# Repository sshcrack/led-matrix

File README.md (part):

<div align="center">

# LED Matrix Controller

**Turn a Raspberry Pi and a few HUB75 LED panels into a calm, good-looking ambient display.**
Aquariums, planets, auroras, music-reactive scenes and self-playing games. Controlled from your phone, with no coding required.

[Quick start](#quick-start) ·
[What is this?](#what-is-this) ·
[Hardware](#hardware) ·
[Install guide](#install-guide) ·
[Desktop app](#desktop-app) ·
[Web UI](#web-ui) ·
[Configuration](#configuration) ·
[Troubleshooting](#troubleshooting) ·
[Development](#development)

</div>

---

## Quick start

> [!IMPORTANT]
> **You need:** a **Raspberry Pi 3 or 4** (the Pi 5 is untested, see [Shopping list](#shopping-list)), a microSD card of **8 GB or more**, HUB75 LED panels, a HUB75 adapter board or HAT, and a separate **5 V supply** for the panels.

| I have… | Do this |
|:--|:--|
| A Pi with panels wired up | Follow the steps below (about 15 minutes, most of it waiting) |
| A Pi already running Raspberry Pi OS that I want to keep | [**Install the package**](#install-on-an-existing-raspberry-pi-os) |
| A Pi with panels, and I'd rather have an AI agent do it | [**Set up with an AI agent**](#set-up-with-an-ai-agent) |
| Nothing yet (no Pi, panels or adapter) | [**Hardware**](#hardware): what to buy and how to wire it |
| Just a computer, no hardware | [**Try the emulator**](#try-it-without-hardware) |

### 1. Flash the card

The panel image is Raspberry Pi OS Lite (64-bit) with everything installed. Its system is read-only, so the panel can be unplugged like any appliance ([details](docs/PI_IMAGE.md)).

1. Download Raspberry Pi Imager and start it with this project's image list, in one command:

   | OS | Run |
   |:--|:--|
   | **Linux / macOS** | `curl -fsSL https://raw.githubusercontent.com/sshcrack/led-matrix/master/scripts/flash_card.sh \| bash` |
   | **Windows** (PowerShell) | `irm https://raw.githubusercontent.com/sshcrack/led-matrix/master/scripts/flash_card.ps1 \| iex` |

   The script ([`flash_card.sh`](scripts/flash_card.sh), [`flash_card.ps1`](scripts/flash_card.ps1)) fetches the current Imager (version 2 or newer; on Linux and macOS it is cached and not installed system-wide) and runs `rpi-imager --repo https://github.com/sshcrack/led-matrix/releases/latest/download/led-matrix-imager.json`. If you already have Imager, run that command yourself, or enter the URL under **App Options → Content Repository → Use custom URL**.
2. Choose your Pi model, then **LED Matrix** as the operating system, and your SD card.
3. In the customisation, set a username and password, your **Wi-Fi** (skip it for Ethernet) and, if you want to log in later, **SSH**. Set the hostname to **`led-matrix`** (Imager may suggest another name), or remember the one you choose.
4. Write the card, put it in the Pi and power it on. The first boot takes a few minutes and restarts once.

The image and its checksum are also on the [Releases](https://github.com/sshcrack/led-matrix/releases/latest) page (`led-matrix-<version>-arm64.img.xz`) if you prefer another flashing tool. Imager is still needed for the Wi-Fi and user settings.

### 2. Set up the panel

Open **`http://led-matrix.local:8080/`** on a phone or computer on the same network (or `http://<pi-ip-address>:8080/`; your router shows the address). On a phone, use *Add to Home Screen* to install it like an app.

The page asks you to **set up your panel**. The image starts with settings for four 64×64 panels in a 2×2 grid (two chains of two, 128×128 pixels) on a Pi 3. On the **Panel hardware** card:
1. Switch on **Show test pattern**. If the picture is already right, press **Looks right** and you are done.
2. Otherwise choose your layout under **Change panel settings**. Use GPIO slowdown `3` for a Pi 3 and `2` for a Pi 4.
3. Apply. The panel restarts with the new settings, and goes back to the old ones by itself if it does not come up.

The settings are right when the red corner is top left, the arrow points up and the white frame runs round the whole picture. Other layouts are in [Working out the numbers](#working-out-the-numbers).

### 3. Use it

1. Press the power button (top right) if the matrix is off.
2. In **Control**, leave the toggle on **Auto** to let the Director pick scenes, or pick **Manual** and click a preset.
3. Press **+** to build a preset: choose a one-tap starting point (Night sky, Digital calm, Desk clock) or pick scenes yourself.
4. Open **Scenes** to browse every scene with an animated preview.

Panels dark, flickering or scrambled? Those are almost always one-flag fixes. See [Troubleshooting](#troubleshooting).

### 4. Optional: the desktop app on your PC

The [desktop app](#desktop-app) adds music reactivity (from your PC's audio output), GPU shader scenes, music videos, and render offload for heavy scenes. It installs for your user only, with no admin rights, and keeps itself on the same version as your matrix.

| OS | Install |
|:--|:--|
| **Windows** | Run `led-matrix-desktop-<version>-win64.exe` from [Releases](https://github.com/sshcrack/led-matrix/releases/latest) |
| **Linux** (x86_64) | `curl -fsSL https://raw.githubusercontent.com/sshcrack/led-matrix/master/scripts/install-desktop.sh \| sh` |

Start it and click **Connect**. It looks for the panel at `led-matrix.local` (port `8080`); enter the Pi's address instead if you changed the hostname or installed the package yourself.

### Install on an existing Raspberry Pi OS

Use this instead of the image when the Pi already runs **64-bit** Raspberry Pi OS (Lite) with a user named **`pi`**.

#### Prepare the Pi (one-time)

SSH into the Pi. Its onboard sound shares hardware with the LED driver, so turn it off, as the upstream library recommends:

```bash
echo "blacklist snd_bcm2835" | sudo tee /etc/modprobe.d/blacklist-rgb-matrix.conf
sudo sed -i 's/^dtparam=audio=on/dtparam=audio=off/' /boot/firmware/config.txt   # /boot/config.txt on older images
sudo reboot
```

#### Install the package

```bash
# Download the installer, read it if you like, then run it
curl -fsSLO https://raw.githubusercontent.com/sshcrack/led-matrix/master/scripts/install_led_matrix.sh
bash install_led_matrix.sh
```

The installer downloads the latest `.deb` from [Releases](https://github.com/sshcrack/led-matrix/releases/latest), installs it and starts the service. It asks for:

| Question | What to answer |
|:--|:--|
| Rows / columns per panel | Panel size, e.g. `64` and `64` |
| Chained panels | Panels daisy-chained on one cable (this sets the width) |
| Parallel chains | Number of cables from the adapter (this sets the height) |
| GPIO slowdown | `3` for a Pi 3, `2` for a Pi 4 |
| Spotify, API token, auto-updates | Optional. You can skip all of them and set them up later |

Four 64×64 panels in a 2×2 grid are `64` / `64` / `2` / `2`. Other layouts are in [Working out the numbers](#working-out-the-numbers).

Then open **`http://<pi-ip-address>:8080/`** (the installer prints the address) and continue with [Use it](#3-use-it).

### Set up with an AI agent

Coding agents (Claude Code, Codex, Cursor, …) can do the whole setup for you, including the interview about your panels. Run the agent on the computer where you want the [desktop app](#desktop-app) (Windows or Linux). If the card isn't flashed yet, it walks you through flashing the panel image with SSH enabled; otherwise make sure you can `ssh` into the Pi from that computer. The agent sets up the Pi over SSH, then installs the desktop app on that computer and connects it to the Pi. Paste:

```text
Set up my LED matrix. Read and follow
https://raw.githubusercontent.com/sshcrack/led-matrix/master/docs/AGENT_SETUP.md
Interview me first, then install and verify everything yourself.
```

The [agent setup guide](docs/AGENT_SETUP.md) is written for machines. It has an interview script that maps your answers to the right flags, a non-interactive install, verification checks, a flicker and colour troubleshooting tree, and rules for handling secrets safely.

### Try it without hardware

The emulator runs the same code as the Pi and shows the matrix in a browser tab, so you can try everything before buying anything. It is built from source (Linux x86_64, see the [build prerequisites](#build-prerequisites)):

```bash
git clone --recurse-submodules https://github.com/sshcrack/led-matrix.git
cd led-matrix
cmake --preset emulator
cmake --build --preset emulator --target install
./scripts/run_web_emulator.sh              # then open http://localhost:8080/web/
```

---

## What is this?

A passive piece of light art for your wall or desk. It runs a growing collection of scenes, picks what to show on its own, and reacts to the music you play. The display shows no tickers and takes no input from viewers. You set it up once and then mostly forget about it.

- **Automatic Mode.** A Director chooses from curated scene looks and composes 24–36 minute visual arcs. While music plays it favours music-reactive scenes. Switch to **Manual** to play your own presets.
- **Follows the real world.** Outdoor scenes match the time of day, weather, season and holidays where the matrix is.
- **Web UI** that works on phones and desktops, installable as a PWA. It has a live 128×128 preview, a scene gallery, a Scene Lab, schedules and diagnostics. See the [tour](#web-ui).
- **Desktop app** (Windows and Linux) for the heavy lifting: GPU shaders, system-audio capture, YouTube music videos. Your PC does the rendering and the Pi just displays pixels. See [Desktop app](#desktop-app).
- **Runs on modest hardware.** Scene quality adapts to the Pi's measured load, and heavy scenes can move to your PC automatically.
- **One `.deb` to install.** A systemd service, safe self-updates with automatic rollback, and a REST API for everything.

```mermaid
flowchart LR
    subgraph Browser["Phone / browser"]
        WEB["Web UI (PWA)"]
    end
    subgraph Pi["Raspberry Pi"]
        D["led-matrix daemon<br/>scenes · Director · REST API"]
        P[("HUB75 LED panels")]
        D -- GPIO --> P
    end
    subgraph PC["Your PC (optional)"]
        APP["Desktop app<br/>audio capture · shaders · video"]
        W["Scene worker<br/>full-quality offload"]
    end
    WEB -- "HTTP + WebSocket :8080" --> D
    APP -- "WebSocket (config, audio analysis)" --> D
    APP -- "UDP pixel stream" --> D
    W -- "rendered frames" --> D
```

---

## Showcase

<div align="center">

<sub>The web UI: Control → Scenes → Lab → Automation → Health, plus the ⌘K palette.</sub>

</div>

<details>
<summary><b>More scene previews</b> (about 10 MB of animated GIFs)</summary>

<br>

Previews are hosted on the rolling [`scene-previews` release](https://github.com/sshcrack/led-matrix/releases/tag/scene-previews) to keep the git history small. The web UI shows all of them.

<div align="center">

<table>
<tr><td align="center"><br><sub><b>Aurora</b> · shader</sub></td><td align="center"><br><sub><b>Tidal Aquarium</b> · shader</sub></td><td align="center"><br><sub><b>Planetary Vista</b> · shader</sub></td><td align="center"><br><sub><b>Volcano</b> · music-reactive</sub></td></tr>
<tr><td align="center"><br><sub><b>Night Drive</b> · music-reactive</sub></td><td align="center"><br><sub><b>Campfire</b> · music-reactive</sub></td><td align="center"><br><sub><b>Lighthouse</b> · music-reactive</sub></td><td align="center"><br><sub><b>Celestial Bloom</b> · music shader</sub></td></tr>
<tr><td align="center"><br><sub><b>Neon Tunnel</b></sub></td><td align="center"><br><sub><b>Reaction Diffusion</b></sub></td><td align="center"><br><sub><b>Metablob</b></sub></td><td align="center"><br><sub><b>Koi Pond</b> · follows the seasons</sub></td></tr>
</table>

</div>

</details>

---

## Hardware

> [!NOTE]
> This project builds on the excellent [rpi-rgb-led-matrix](https://github.com/hzeller/rpi-rgb-led-matrix) library by Henner Zeller. For wiring diagrams, timing issues and panel quirks, its documentation is the reference.

### Shopping list

| Part | Recommendation |
|:--|:--|
| **Computer** | **Raspberry Pi 4** (best), or Pi 3 B/B+ (works, and the maintainer's 128×128 runs on a Pi 3 B with adaptive quality and desktop offload). A 64-bit OS is required. The Pi 5 is supported by the LED library since [v0.1.13](https://github.com/sshcrack/rpi-rgb-led-matrix/releases/tag/v0.1.13) (RP1 backend, `--led-rp1-pio`), but this app has not been tested on one. |
| **Panels** | HUB75 RGB panels. **Four 64×64 panels in a 2×2 grid make a 128×128 display**, which is the primary target. 32×32 and 64×32 panels work too, and scenes read the canvas size. |
| **Adapter** | A HAT or bonnet that level-shifts GPIO to HUB75, e.g. the [Electrodragon Active-3](https://www.electrodragon.com/product/rgb-matrix-panel-drive-board-raspberry-pi/). [Alternatives](https://github.com/hzeller/rpi-rgb-led-matrix/blob/master/adapter/README.md). |
| **Power** | A dedicated **5 V** supply for the panels, sized generously. Panels can draw several amps each at full white. Power the Pi separately and share ground. Don't power panels from the Pi. |
| **Cables** | The HUB75 ribbon cables that come with the panels, plus power leads for each panel. |
| **Storage** | A microSD card, 16 GB or more. |

### Working out the numbers

The matrix size is **width = `cols` × `chain`** and **height = `rows` × `parallel`**.

| Layout | rows | cols | chain | parallel | Result |
|:--|:-:|:-:|:-:|:-:|:--|
| Four 64×64 panels, 2×2 *(recommended)* | 64 | 64 | 2 | 2 | 128×128 |
| One 64×64 panel | 64 | 64 | 1 | 1 | 64×64 |
| Two 64×32 panels side by side | 32 | 64 | 2 | 1 | 128×32 |
| Four 32×32 panels in a row | 32 | 32 | 4 | 1 | 128×32 |

The installer asks for these. They end up as `--led-rows`, `--led-cols`, `--led-chain` and `--led-parallel` in `/etc/default/led-matrix`. How many parallel chains your adapter supports depends on the adapter, so check its documentation. The Active-3 has three parallel outputs.

### Assemble and wire

1. Plug the **adapter or HAT** onto the Pi's 40-pin header (Pi switched off and unplugged).
2. Connect the adapter's HUB75 output to the **input** of the first panel with the ribbon cable. Panels have an *in* and an *out* side, usually marked with an arrow.
3. For more panels on the same chain, run a ribbon from the first panel's **output** to the next panel's **input**. Use a second adapter output for a second (parallel) chain. Which output is which depends on the adapter, so check its documentation, or the upstream [wiring guide](https://github.com/hzeller/rpi-rgb-led-matrix/blob/master/wiring.md).
4. Connect the **5 V supply** to every panel's power connector (use the supplied power leads). Power the Pi from its own supply. Power everything off before changing any cable.

### Flash the Pi

Flash the panel image as described in [Flash the card](#1-flash-the-card). To use plain Raspberry Pi OS instead, choose **Raspberry Pi OS Lite (64-bit)** in Imager, set the username **`pi`**, Wi-Fi and SSH in its customisation, and continue with [Install on an existing Raspberry Pi OS](#install-on-an-existing-raspberry-pi-os).

> [!TIP]
> Prefer not to do this alone? Your [AI agent](#set-up-with-an-ai-agent) can walk you through every step above and run the commands over SSH.

---

## Install guide

The [Quick start](#quick-start) covers a normal install. This section is the reference for what gets installed and how to change, update or remove it.

### Requirements

- Raspberry Pi 3 or 4 (Pi 5 untested) with a **64-bit** Debian-based OS (Debian 12 "Bookworm" or newer), a user named **`pi`**, and internet access
- Panels wired and powered (see [Hardware](#hardware))
- The Pi's onboard sound disabled ([Prepare the Pi](#prepare-the-pi-one-time))

### Install

Use the [installer script](#install-the-package), or install the package yourself:

```bash
# Download led-matrix-<version>_arm64.deb from the latest release, then:
sudo apt install ./led-matrix-*_arm64.deb
```

Either way, the package:

- installs the daemon to `/usr/bin/led-matrix`, with plugins, web UI and previews under `/usr/lib/led-matrix` and `/usr/share/led-matrix`
- writes your answers to `/etc/default/led-matrix`
- creates `/var/lib/led-matrix/` (config, uploads, crash reports), owned by `pi`
- enables and starts `led-matrix.service` and the updater units

The service starts as root (needed for GPIO) and drops privileges to `pi:pi` as soon as the matrix is initialised.

### Check that it works

```bash
systemctl status led-matrix          # should be active (running)
curl -s localhost:8080/status        # {"turned_on":true, ...}
journalctl -u led-matrix -f          # live logs
```

### Change settings later

> [!IMPORTANT]
> `/etc/default/led-matrix` is **regenerated from the stored answers on every upgrade and reconfigure**, so manual edits to it are lost. Change settings through debconf.

```bash
sudo dpkg-reconfigure led-matrix     # re-asks every question
```

Or non-interactively:

```bash
echo "led-matrix led-matrix/led-slowdown-gpio string 2" | sudo debconf-set-selections
echo "led-matrix led-matrix/extra-opts string --led-brightness=60" | sudo debconf-set-selections
sudo DEBIAN_FRONTEND=noninteractive dpkg-reconfigure led-matrix
```

Any extra [rpi-rgb-led-matrix flag](https://github.com/hzeller/rpi-rgb-led-matrix?tab=readme-ov-file#types-of-displays) goes in `extra-opts`.

### Update and uninstall

Updates run automatically if you enabled them. You can also use the **Updates** page or `POST /api/update/install`. Each update is unpacked as its own version in `/var/lib/led-matrix-app` and switched to in one step; a version that does not come up healthy is switched back automatically ([details](docs/transactional-updates.md)). Manually: install a newer `.deb` with `sudo apt install ./led-matrix-*.deb`.

```bash
sudo apt remove led-matrix           # keep your data
sudo apt purge led-matrix            # also removes /var/lib/led-matrix and the stored answers
```

### Power-cut-safe card (optional)

The [panel image](#1-flash-the-card) is already power-cut-safe. To move an existing install to such a card, `packaging/pi-image/` exports the settings from the running Pi and builds an image with them. See [docs/PI_IMAGE.md](docs/PI_IMAGE.md). Updates of the app work as usual there (they go to the data partition); OS updates go through `sudo led-matrix-system-mode writable`.

---

## Desktop app

The Pi is deliberately modest. The **desktop app** gives it superpowers by running on a PC on the same network:

| It adds… | How it works |
|:--|:--|
| **Music reactivity** | Captures your system's audio output (WASAPI loopback on Windows, PipeWire/PulseAudio monitor on Linux), analyses it (spectrum, beats, drops, BPM, sections) and streams the result to the Pi. No microphone needed. |
| **GPU shaders** | Renders the `shader:*` scenes (Aurora, Aquarium, Planetary Vista…) and streams pixels to the Pi over UDP. Custom `.frag` files can be uploaded in the web UI under **Assets**. |
| **Video and music videos** | `video` plays YouTube and URL videos, and `spotifymv` auto-plays the music video for your current Spotify track. Needs [`yt-dlp`](https://github.com/yt-dlp/yt-dlp) and ffmpeg on the PC. |
| **Render offload** | A background scene worker runs the same scene code at full quality when the Pi is under pressure. The handoff is seamless, with local fallback if the worker disappears. |

<table>
<tr>
<td width="50%"><br><sub>Connected, with audio analysis streaming.</sub></td>
<td width="50%"><br><sub>The scene worker is running and ready to take over heavy scenes.</sub></td>
</tr>
</table>

### Install

Grab the latest build from [Releases](https://github.com/sshcrack/led-matrix/releases/latest):

| OS | Install (for your user, no admin/root) |
|:--|:--|
| **Windows** | Run `led-matrix-desktop-<version>-win64.exe`, or `irm https://raw.githubusercontent.com/sshcrack/led-matrix/master/scripts/install-desktop.ps1 \| iex` |
| **Linux** (x86_64) | `curl -fsSL https://raw.githubusercontent.com/sshcrack/led-matrix/master/scripts/install-desktop.sh \| sh` (add `-s -- <version>` after `sh` for a specific version). Or download `led-matrix-desktop-<version>-Linux.tar.gz`, extract it and run `bin/led-matrix-desktop --install` |

On Linux the installer adds a launcher entry and `~/.local/bin/led-matrix-desktop`; put `~/.local/bin` on your `PATH` to start it from a terminal.

The app installs to `%LOCALAPPDATA%\led-matrix-desktop` or `~/.local/share/led-matrix-desktop` and **updates itself**: it runs the same release as your matrix (offload requires compatible protocol and scene contracts). When a newer release is out and the matrix has auto-update on, it asks the matrix to update first and follows it. Updates download in the background and apply when the app is hidden in the tray or restarted. You can turn this off in the app menu. An older `.deb` or admin install is replaced on its first update, and the app offers to remove it. Uninstall with `led-matrix-desktop --uninstall` or from Windows *Installed apps*.

### Use

1. Start the app, enter the Pi's **hostname or IP** and the **port** (`8080`), and add the **API token** if you set one.
2. Click **Connect**. The status switches to *WebSocket is currently: Open* and the plugin tabs show what is active.
3. Leave it running in the tray. Enable *Turn Matrix On on Start* if you like.

The app needs to be connected for shader scenes, desktop audio, videos and render offload. Everything else keeps working without it.

---

## Web UI

Open `http://<pi-ip>:8080/` in any browser. On a phone, use *Add to Home Screen* to install it like an app.

<table>
<tr>
<td width="50%"><br><b>Control.</b> Presets, the live preview, and a one-click Auto/Manual switch. The inspector edits the selected preset in place and autosaves.</td>
<td width="50%"><br><b>Scenes.</b> Browse every scene with animated previews. Tune what the Director may play: favourite a look, keep it, or switch it off.</td>
</tr>
<tr>
<td><br><b>Lab.</b> Try scenes on the real Pi renderer with temporary controls. Nothing is saved until you decide.</td>
<td><br><b>Automation.</b> Time-of-day schedules and a night-brightness fade.</td>
</tr>
<tr>
<td><br><b>Health.</b> Renderer FPS, transport stats, and a transparent view of why the Director chose what it chose.</td>
<td><br><b>Quick builder.</b> Create <i>and play</i> a preset in one step from one-tap starting points or any scenes you pick.</td>
</tr>
</table>

Press <kbd>Ctrl</kbd>/<kbd>⌘</kbd>+<kbd>K</kbd> anywhere for the command palette, and use the sun/moon button for the light theme.

<details>
<summary><b>On your phone, and in light mode</b></summary>

<br>

<div align="center">

<br><br>

</div>

On screens narrower than 1024 px the layout switches to a bottom tab bar with an always-visible mini-player, and editors open as bottom sheets.

</details>

---

## Features

### Scenes

Scenes are supplied by plugins. Native scenes render on the Pi or desktop worker; shader and video scenes need the desktop app. Browse **Scenes** in the web UI for the installed catalog.

| Category | Highlights |
|:--|:--|
| **Audio reactive** | A spectrum analyser and small scenic worlds that dance to the music: campfire, volcano, lighthouse, reef, skate park, tesla coil, night drive, roller rink… plus `music_director`, an automatic DJ |
| **Shaders** | GPU scenes rendered on your PC: Aurora, Tidal Aquarium, Planetary Vista, Plasma Garden, and music shaders (Celestial Bloom, Subwoofer, Tube Amp…). Add your own `.frag` files |
| **Hobbies & activities** | Hiking trails and an alpine lake, horses in the mist, basketball and football, and cycling a coast road or skiing a slope |
| **Ambient** | A forest path and a cottage that change with the seasons, a Christmas market and a sleigh over a snowy village (December only in Automatic Mode), a starling murmuration over a wetland at dusk, plus Starfield, Metablob, Clock, Neon Tunnel, Rain |
| **Games** | Self-playing Tetris |
| **Generative** | Reaction-diffusion, Falling Sand, Watermelon Plasma |
| **Fractals** | Julia set, Game of Life |
| **Particles** | Rain, Sparks |
| **Media** | YouTube music videos that follow your Spotify track, a video player, and Spotify cover art when connected |
| **Weather** | Live weather (via Open-Meteo, no API key) |
| **Utility / Images** | Countdown with fireworks, and a pixel-art and image provider |

Plus **7 post-processing effects** (flash, rotate, glow, RGB split, glitch, pixelate, shockwave; they can fire on beats) and **11 transitions** (blend, swipe, morph, radial reveal, dissolves, CRT collapse, …).

### Control

| Feature | What it does |
|:--|:--|
| **Automatic Mode** | The Director picks from curated looks, plans long arcs, and uses music state when it is available. Every look can be starred or excluded in the Scenes page. Pick a style on the home screen: **Mixed** (everything, music first), **Outside** (calm scenery that matches the real time, weather, season and holidays), **Party** (energetic music looks, quicker cuts) or **Chill** (slow and soft, long dwell). Holiday scenes such as the Christmas market only play while their holiday is on. |
| **Presets** | Ordered lists of scenes with per-scene properties and transitions. Edits autosave, and deleting a preset can be undone. Three one-tap ambiance packs are included. |
| **Scene Lab** | Try a scene or curated look on the real Pi renderer with temporary controls, then save it only if you like it. |
| **Schedules** | Switch presets by time and weekday (overnight ranges work) and dim the panel at night with a smooth brightness fade. While *Auto Scheduling* is on, an active schedule takes over from Automatic Mode, and the display turns **off** outside every schedule window. Add windows for all the hours you want lit, or leave it off. |
| **Real-world scenery** | Outdoor scenes follow the real time of day, weather and season where the matrix is: sunset light, rain, fog, snow on the ground, autumn leaves, decorations at Christmas. The location is detected from the IP address or set by city. You can override it for every scene (snow all winter, always night) or pin a single scene, or turn it off. See [Real-world scenery](#real-world-scenery-optional). |
| **Live preview** | A real-time view of the composed matrix frame, pulled on demand so an idle page costs the Pi nothing. |
| **Plugin UIs** | Plugins can ship their own web controls, for example the YouTube playlist editor. |
| **Safe updates** | Check and install updates from the UI. The updater health-checks the new version and rolls back automatically on failure ([details](docs/transactional-updates.md)). The desktop app updates itself to the same release. |
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
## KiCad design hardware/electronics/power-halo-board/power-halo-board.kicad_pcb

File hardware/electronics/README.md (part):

# Electronics: power distribution and halo controller

Status: **prototype design, unvalidated, not approved for fabrication.** Nothing here has been
built or measured. The outputs in `exports/` are marked PROTOTYPE / UNVALIDATED.
[docs/verification.md](docs/verification.md) lists what was checked and what is still open.

## Architecture

The display uses a 2×2 grid of Waveshare P3 64×64 HUB75E panels (1/32 scan, 5 V / 4 A, at most
20 W each). It is driven by a Raspberry Pi 3B through the existing software:
`--led-rows=64 --led-cols=64 --led-chain=2 --led-parallel=2`, the default (`regular`) GPIO
mapping, and address lines A–E.

The design uses **one custom board** plus off-the-shelf parts:

| Part | What it is | Custom? |
|---|---|---|
| 24 V supply | Mean Well GST160A24-R7B: external Class I brick, 160 W, 4-pin power DIN plug | no |
| Enclosure jack | Kycon KPJX-PM-4S panel-mount 4-pin power DIN jack, AWG18 pigtail to J1 | no |
| **Power + halo board** | `power-halo-board/`, 136 × 86 mm, 4 layers | **yes** |
| HUB75 interface | Electrodragon RGB matrix driver board for Raspberry Pi, V2 (the board the main README links) | no |
| Controller | Raspberry Pi 3B (Wi-Fi only) | no |
| Halo | 40 × WS2812B-class LEDs on one 5 V data line | no |

```
230 V ─ brick (outside the enclosure, 24 V SELV) ─ DIN jack ─ AWG18 ─ J1
  J1 ─ F1 8 A ─ LM74700 + PSMN5R2 ideal diode ─ SMBJ30A + bulk ─ +24V
  +24V ─ 4× TPSM63610 → 5.0 V ─ TPS259470A eFuse (5.0 A) ─ J101..J401 ─ panel 1..4 power
  +24V ─ TPSM63610 AUX → +5V_AUX ─┬─ TPS259470A (3.0 A) ─ J501 ─ Electrodragon 5 V in ─ Pi
                                  ├─ TPS259470A (2.6 A, MCU-enabled) ─ J601 ─ halo (+5V, DIN, GND)
                                  └─ ATtiny1616, AHCT buffer, LEDs
  Pi GPIO14 (TXD) ─ 1k ─ AHCT1G125 ─ ATtiny1616 UART RX       (halo commands)
  Pi GPIO26 ─ 1k ─ JP601 ─ BSS138 ×2 ─ EN of the four panel bucks (panel request)
```

Why one board: the brick keeps mains out of the enclosure. The Electrodragon V2 already
buffers HUB75 for two parallel chains with the E line, so a custom HUB75 board would add
nothing. What is missing is protected 5 V power for 85 W of panels plus the Pi and halo, and a
halo driver that uses no matrix pins. One board does both. The decisions behind this:

- **24 V distribution** instead of a 5 V brick. One 5 V rail would carry 18 A or more through
  connectors and wiring. At 24 V the input carries 4.9 A worst case. Each panel gets its own
  converter and its own limit.
- **Hardware current limit per output.** Each panel branch has an eFuse limited to 5.0 A ±10 %
  (the panel is rated 4 A). The Pi and halo branches are limited to 3.0 A and 2.6 A. Software
  brightness limits are not counted as protection anywhere.
- **No backfeed.** Every 5 V output eFuse blocks reverse current. The Pi logic lines only sink
  into the board through 1 kΩ resistors and high-impedance inputs. The board never drives a Pi
  pin.
- **Halo without matrix pins.** It uses GPIO14 (UART TXD) and GPIO26. With
  `--led-parallel=2` the library leaves chain-3 pins free (GPIO 2, 3, 14, 16, 21, 26). The
  ATtiny1616 generates the WS2812 timing, so the Pi only sends short UART commands. The halo
  must never be fed by continuously pushed `/live_frame` capture. The API preview stays
  pull-only.
- **Electrodragon V2 is fine with conditions** (see [docs/wiring.md](docs/wiring.md#hub75-and-the-electrodragon-v2)):
  - Set the E-line selector so pin 8 carries E and pin 4 is GND.
  - Leave its third HUB75 output (P2) unconnected.
  - Power it only from J501.

## Files

| Path | Content |
|---|---|
| `power-halo-board/` | KiCad 9 project: hierarchical schematic (root + Input, Panel ×4, Aux, Halo), routed PCB, project-local symbol and footprint library `lib/`, net classes and rules (`.kicad_pro`, `.kicad_dru`) |
| `power-halo-board/lib/3dmodels/` | VRML envelope boxes for the parts the stock KiCad libraries reference but never shipped a model for (see `tools/gen_3dmodels.py`) |
| `tools/circuit.py` | the circuit as data: every part with value, MPN, manufacturer, datasheet, rating and pin-to-net map |
| `tools/gen_lib.py`, `gen_sch.py`, `gen_project.py` | write the library, schematic and project files from `circuit.py` |
| `tools/gen_pcb.py` | placement, power zones, Freerouting autorouting, ground pours, stitching, silkscreen |
| `tools/check_board.py` | ERC, independent netlist check, DRC with schematic parity, prototype exports |
| `tools/check_netlist.py` | checks every pin-to-net connection of the exported netlist against `circuit.py` |
| `tools/spice/` | ngspice decks (thresholds, enable sequence, hot-plug), runner and `results.txt` |
| `tools/power_budget.py` | worst-case power and thermal budget |
| `tools/gen_envelope.py` | height envelope and plug keepouts as JSON and STEP for the enclosure |
| `tools/gen_3dmodels.py` | `lib/3dmodels/`: envelope box per part whose stock KiCad 3D model does not exist, so the 3D viewer shows every component |
| `docs/wiring.md` | harnesses, pinouts, keying, wire gauge, strain relief, HUB75 and the Electrodragon V2 |
| `docs/power-and-thermal.md` | supply choice, rails and loads, protection, thermal budget, ventilation |
| `docs/mechanical-interface.md` | outline, holes, connector positions and directions, heights, keepouts |
| `docs/verification.md` | what was verified, with results, and the open gaps |
| `docs/bom.csv` | BOM (copied from the export) |

## Board

- 136 × 86 mm, 1.6 mm FR4, 4 layers, ENIG.
- Copper is 2 oz on the outer layers and 1 oz on the inner layers.
- Layers:
  - F.Cu: components, +24 V and 5 V power zones.
  - In1: solid GND.
  - In2: +5V_AUX plane regions, GND elsewhere.
  - B.Cu: signals and a GND pour.
- Net classes:
  - `Power24`: +24V and VIN_*, 0.5 mm, 0.3 mm clearance.
  - `Power5`: panel VOUT/VPANEL, VPI and VHALO, 0.4 mm.
  - `GND`, `Power5AUX`, `Default`: 0.2 mm.
- Custom rules: 24 V clearance 0.3 mm, minimum 0.4 mm power taps, 0.5 mm copper-to-edge.
  Autorouted tracks and vias are additionally kept 0.85 mm from the edge by rule areas.
- The committed `.kicad_pcb` has its **zones unfilled**: filled it is about 1.9 MB, against the
  repo's 2 MiB per-file guard. Press `B` in KiCad, or use `exports/power-halo-board-filled.kicad_pcb`.

## Regenerating

Requires KiCad 9 (`kicad-cli` and the `pcbnew` Python module), KiCad's 3D models
(`kicad-packages3d`, for the 3D viewer and `kicad-cli pcb render`), ngspice, Java 21+, xvfb-run and
Freerouting 1.9.0. The jar is not committed: set `FREEROUTING_JAR`, or place it at
`tools/freerouting-1.9.0.jar`. Freerouting runs headless with analytics off, but checks for new
versions online at startup. `LEDPANEL_SCRATCH` sets its work directory (default
`.route/`, git-ignored).

```bash
cd hardware/electronics
python3 tools/gen_3dmodels.py     # 3D models for the parts KiCad does not model
python3 tools/gen_lib.py && python3 tools/gen_sch.py && python3 tools/gen_project.py
mkdir -p .route && kicad-cli sch export netlist -o .route/net.net power-halo-board/power-halo-board.kicad_sch
python3 tools/gen_pcb.py place .route/net.net
python3 tools/gen_pcb.py route     # Freerouting; retried until all nets are connected
python3 tools/gen_pcb.py finish    # pours, stitching, silkscreen, title block, stackup
python3 tools/check_board.py       # ERC + netlist + DRC/parity, then exports/ (exit 1 on any failure)
python3 tools/spice/run_spice.py
python3 tools/power_budget.py
python3 tools/gen_envelope.py && <python with cadquery> tools/gen_envelope.py --step
```

Freerouting is not deterministic. A new `route` run gives different tracks, so the finished
board is committed. `finish` reuses the last route in the scratch directory
(`routed.kicad_pcb`). Re-run `place` and `route` only after placement or netlist changes.
Hand edits in KiCad are fine: `check_board.py` verifies whatever board is committed.

## Outputs (git-ignored `exports/`)

`check_board.py` writes:

- The schematic PDF and BOM CSV.
- Board PDFs: top, bottom, in1, in2, assembly.
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
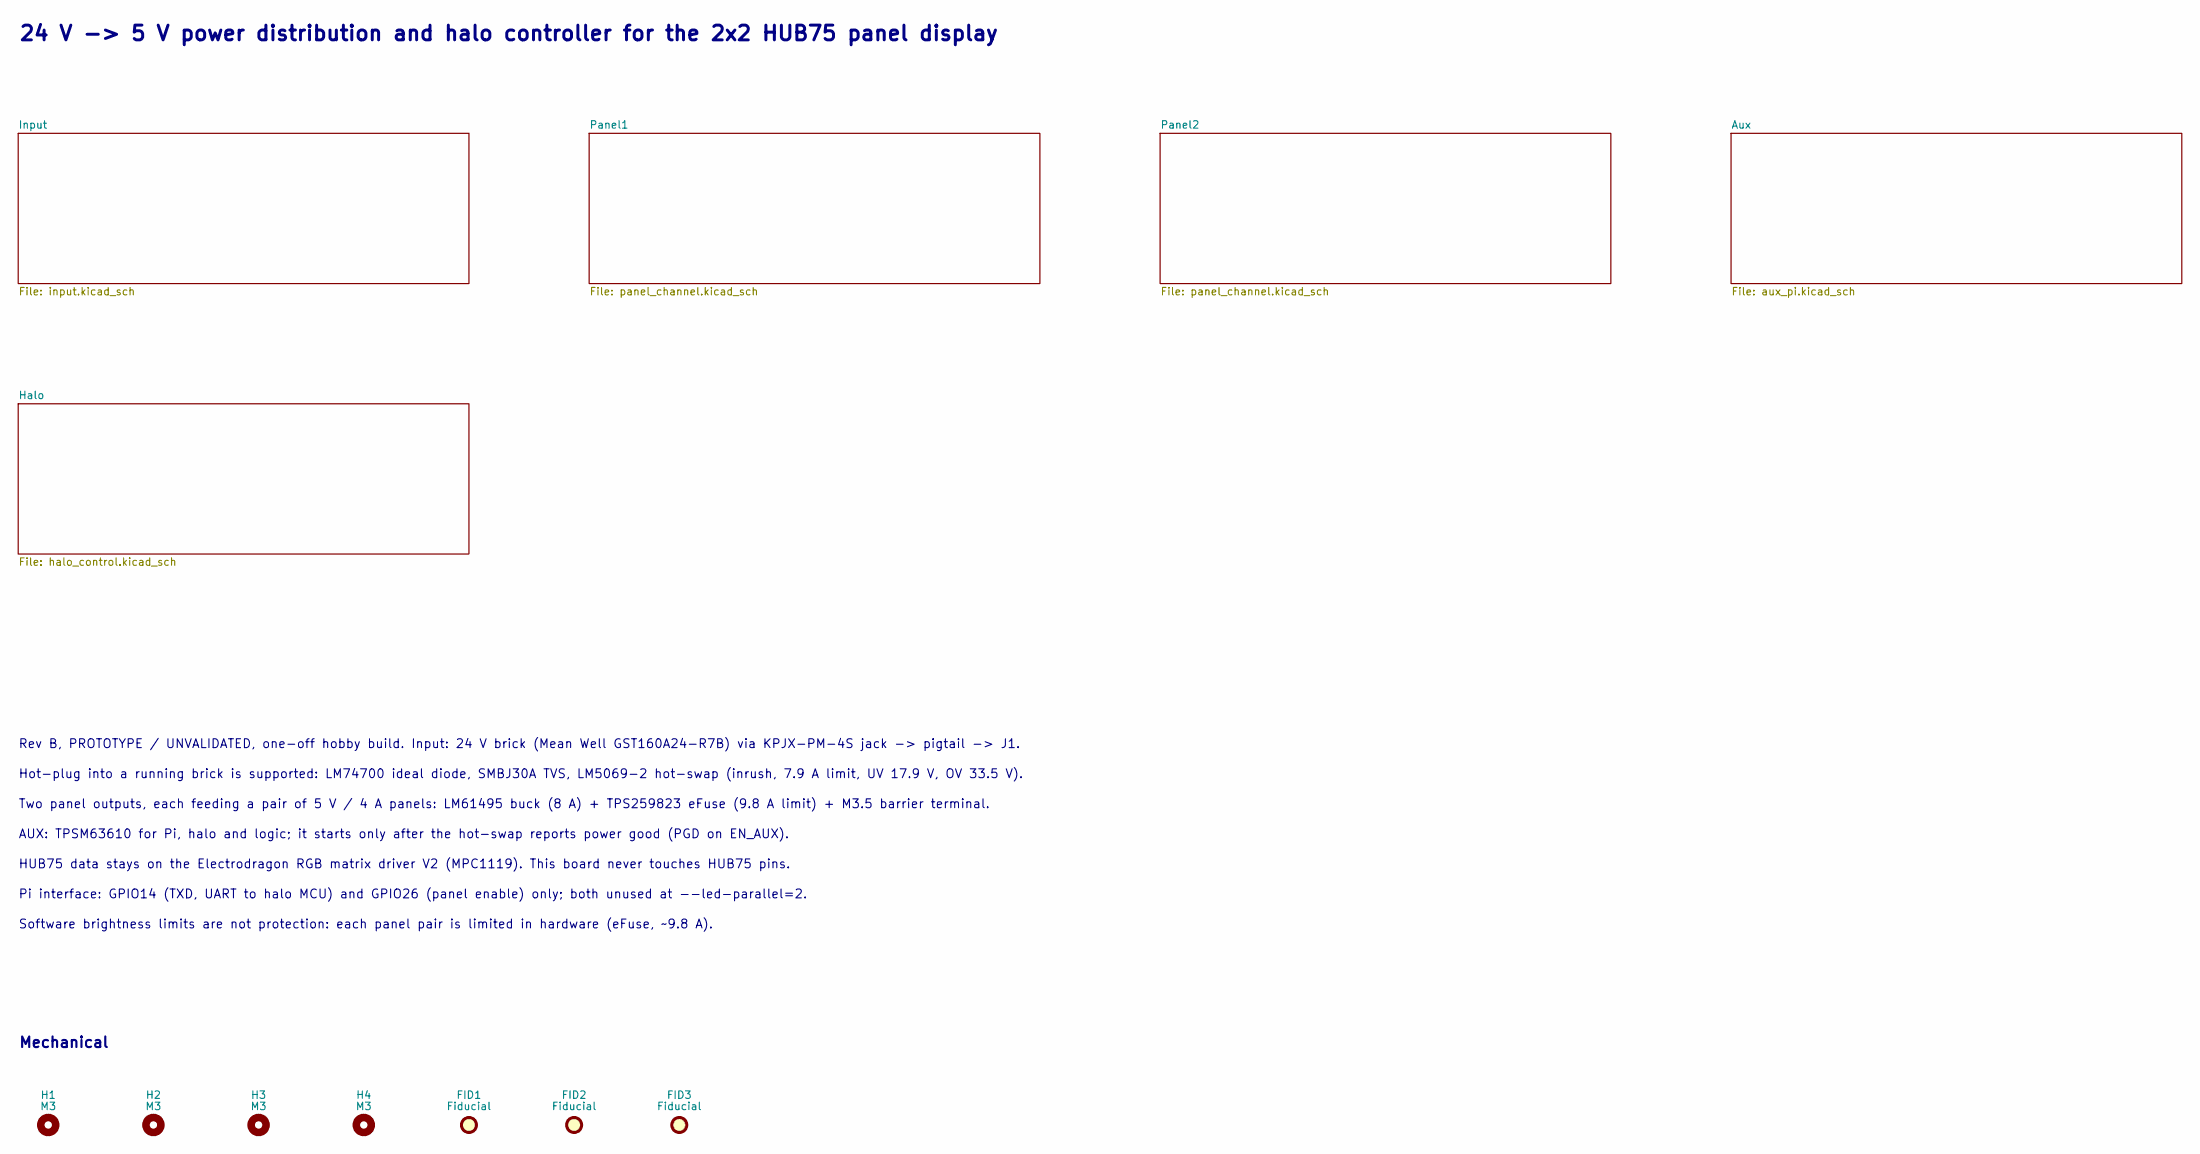
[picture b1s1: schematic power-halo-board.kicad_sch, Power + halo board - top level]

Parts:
FID1, FID2, FID3: Fiducial; Fiducial_1mm_Mask2mm
H1, H2, H3, H4: M3; MountingHole_3.2mm_M3

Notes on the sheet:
24 V -> 5 V power distribution and halo controller for the 2x2 HUB75 panel display
Rev B, PROTOTYPE / UNVALIDATED, one-off hobby build. Input: 24 V brick (Mean Well GST160A24-R7B) via KPJX-PM-4S jack -> pigtail -> J1.
Hot-plug into a running brick is supported: LM74700 ideal diode, SMBJ30A TVS, LM5069-2 hot-swap (inrush, 7.9 A limit, UV 17.9 V, OV 33.5 V).
Two panel outputs, each feeding a pair of 5 V / 4 A panels: LM61495 buck (8 A) + TPS259823 eFuse (9.8 A limit) + M3.5 barrier terminal.
AUX: TPSM63610 for Pi, halo and logic; it starts only after the hot-swap reports power good (PGD on EN_AUX).
HUB75 data stays on the Electrodragon RGB matrix driver V2 (MPC1119). This board never touches HUB75 pins.
Pi interface: GPIO14 (TXD, UART to halo MCU) and GPIO26 (panel enable) only; both unused at --led-parallel=2.
Software brightness limits are not protection: each panel pair is limited in hardware (eFuse, ~9.8 A).
Mechanical

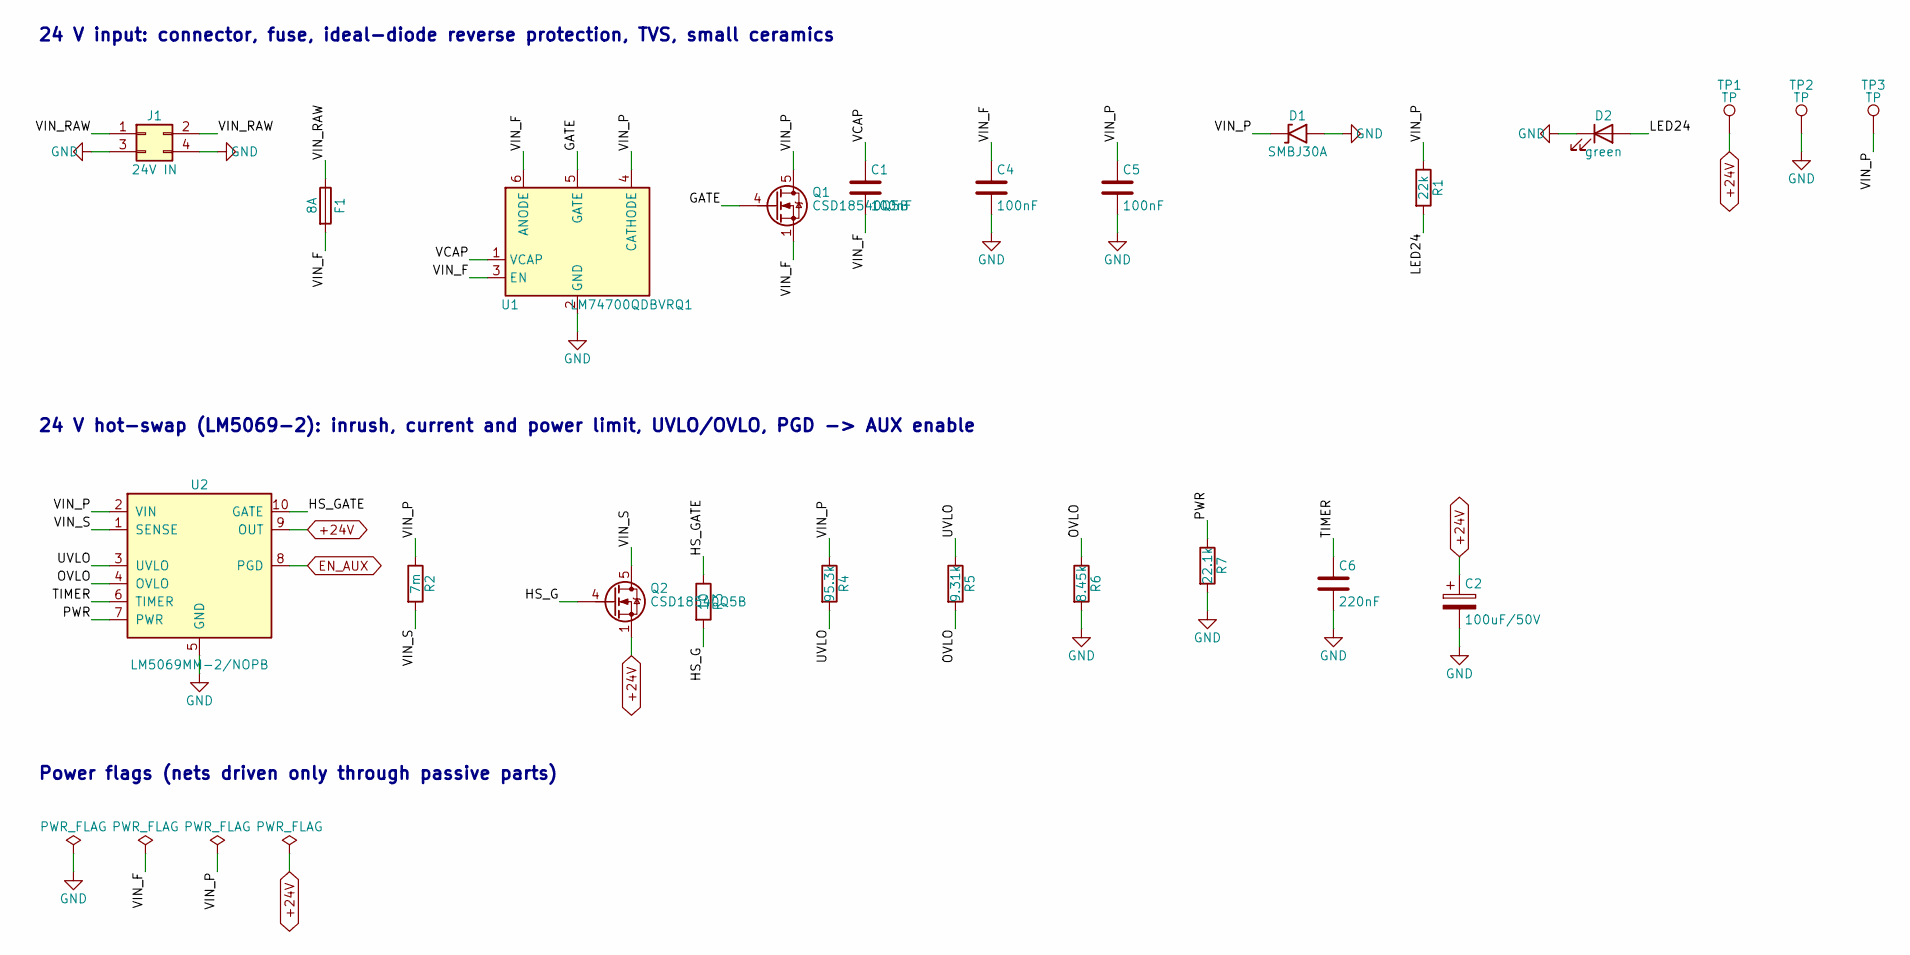
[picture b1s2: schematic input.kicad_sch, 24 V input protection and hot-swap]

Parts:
C1, C4, C5: 100nF; C_0603_1608Metric; Rating 50 V X7R; MPN GRM188R71H104KA93D
C2: 100uF/50V; CP_Elec_8x10; Rating 50V; MPN EEE-FK1H101P
C6: 220nF; C_0603_1608Metric; Rating 50 V X7R; MPN GRM188R71H224KA93D
D1: SMBJ30A; D_SMB; Rating VRWM 30 V, VBR 33.3-36.8 V, VC 48.4 V a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; MPN SMBJ30A
D2: green; LED_0603_1608Metric; Rating 20 mA max, run at ~2 mA; MPN APT1608SGC
F1: 8A; Fuse_Littelfuse-NANO2-451_453; Rating 8 A, very fast, melting I2t 20.23 A2s (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; MPN 0453008.MR
J1: 24V IN; Molex_Mini-Fit_Jr_5569-04A2_2x02_P4.20mm_Horizontal; Rating Mini-Fit Jr: up to 9 A/circuit with 16-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; MPN 39-30-0040
Q1, Q2: CSD18540Q5B; TDSON-8-1; Rating 60 V, 1.8 mOhm (10 V), +-20 V VGS, RthJ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; MPN CSD18540Q5B
R1: 22k; R_0603_1608Metric; Tolerance 1%; Rating 0.1 W, 75 V; MPN RC0603FR-0722KL
R2: 7m; R_2512_6332Metric; Rating 1 W at 70 C, +-75 ppm/K; Tolerance 1%; MPN WSL2512R0070FEA
R3: 10; R_0603_1608Metric; Tolerance 1%; Rating 0.1 W, 75 V; MPN RC0603FR-0710RL
R4: 95.3k; R_0603_1608Metric; Tolerance 1%; Rating 0.1 W, 75 V; MPN RC0603FR-0795K3L
R5: 9.31k; R_0603_1608Metric; Tolerance 1%; Rating 0.1 W, 75 V; MPN RC0603FR-079K31L
R6: 8.45k; R_0603_1608Metric; Tolerance 1%; Rating 0.1 W, 75 V; MPN RC0603FR-078K45L
R7: 22.1k; R_0603_1608Metric; Tolerance 1%; Rating 0.1 W, 75 V; MPN RC0603FR-0722K1L
TP1, TP2, TP3: TP; TestPoint_Pad_D1.5mm
U1: LM74700QDBVRQ1; SOT-23-6; Rating ANODE +-65 V, CATHODE-ANODE -5..75 V ab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; MPN LM74700QDBVRQ1
U2: LM5069MM-2/NOPB; VSSOP-10_3x3mm_P0.5mm; Rating VIN 9-80 V (100 V abs), OVLO pin 7 V abs; MPN LM5069MM-2/NOPB

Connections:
+24V: C2.1, Q2.1 (S), Q2.2 (S), Q2.3 (S), TP1.1, U2.9 (OUT); also elsewhere on the board
/Input/GATE: Q1.4 (G), U1.5 (GATE)
/Input/HS_G: Q2.4 (G), R3.2
/Input/HS_GATE: R3.1, U2.10 (GATE)
/Input/LED24: D2.2 (A), R1.2
/Input/OVLO: R5.2, R6.1, U2.4 (OVLO)
/Input/PWR: R7.1, U2.7 (PWR)
/Input/TIMER: C6.1, U2.6 (TIMER)
/Input/UVLO: R4.2, R5.1, U2.3 (UVLO)
/Input/VCAP: C1.1, U1.1 (VCAP)
/Input/VIN_F: C1.2, C4.1, F1.2, Q1.1 (S), Q1.2 (S), Q1.3 (S), U1.3 (EN), U1.6 (ANODE)
/Input/VIN_P: C5.1, D1.1 (K), Q1.5 (D), R1.1, R2.1, R4.1, TP3.1, U1.4 (CATHODE), U2.2 (VIN)
/Input/VIN_RAW: F1.1, J1.1, J1.2
/Input/VIN_S: Q2.5 (D), R2.2, U2.1 (SENSE)
EN_AUX: U2.8 (PGD); also elsewhere on the board
GND: C2.2, C4.2, C5.2, C6.2, D1.2 (A), D2.1 (K), J1.3, J1.4, R6.2, R7.2, TP2.1, U1.2 (GND), U2.5 (GND); also elsewhere on the board

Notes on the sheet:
24 V input: connector, fuse, ideal-diode reverse protection, TVS, small ceramics
24 V hot-swap (LM5069-2): inrush, current and power limit, UVLO/OVLO, PGD -> AUX enable
Power flags (nets driven only through passive parts)

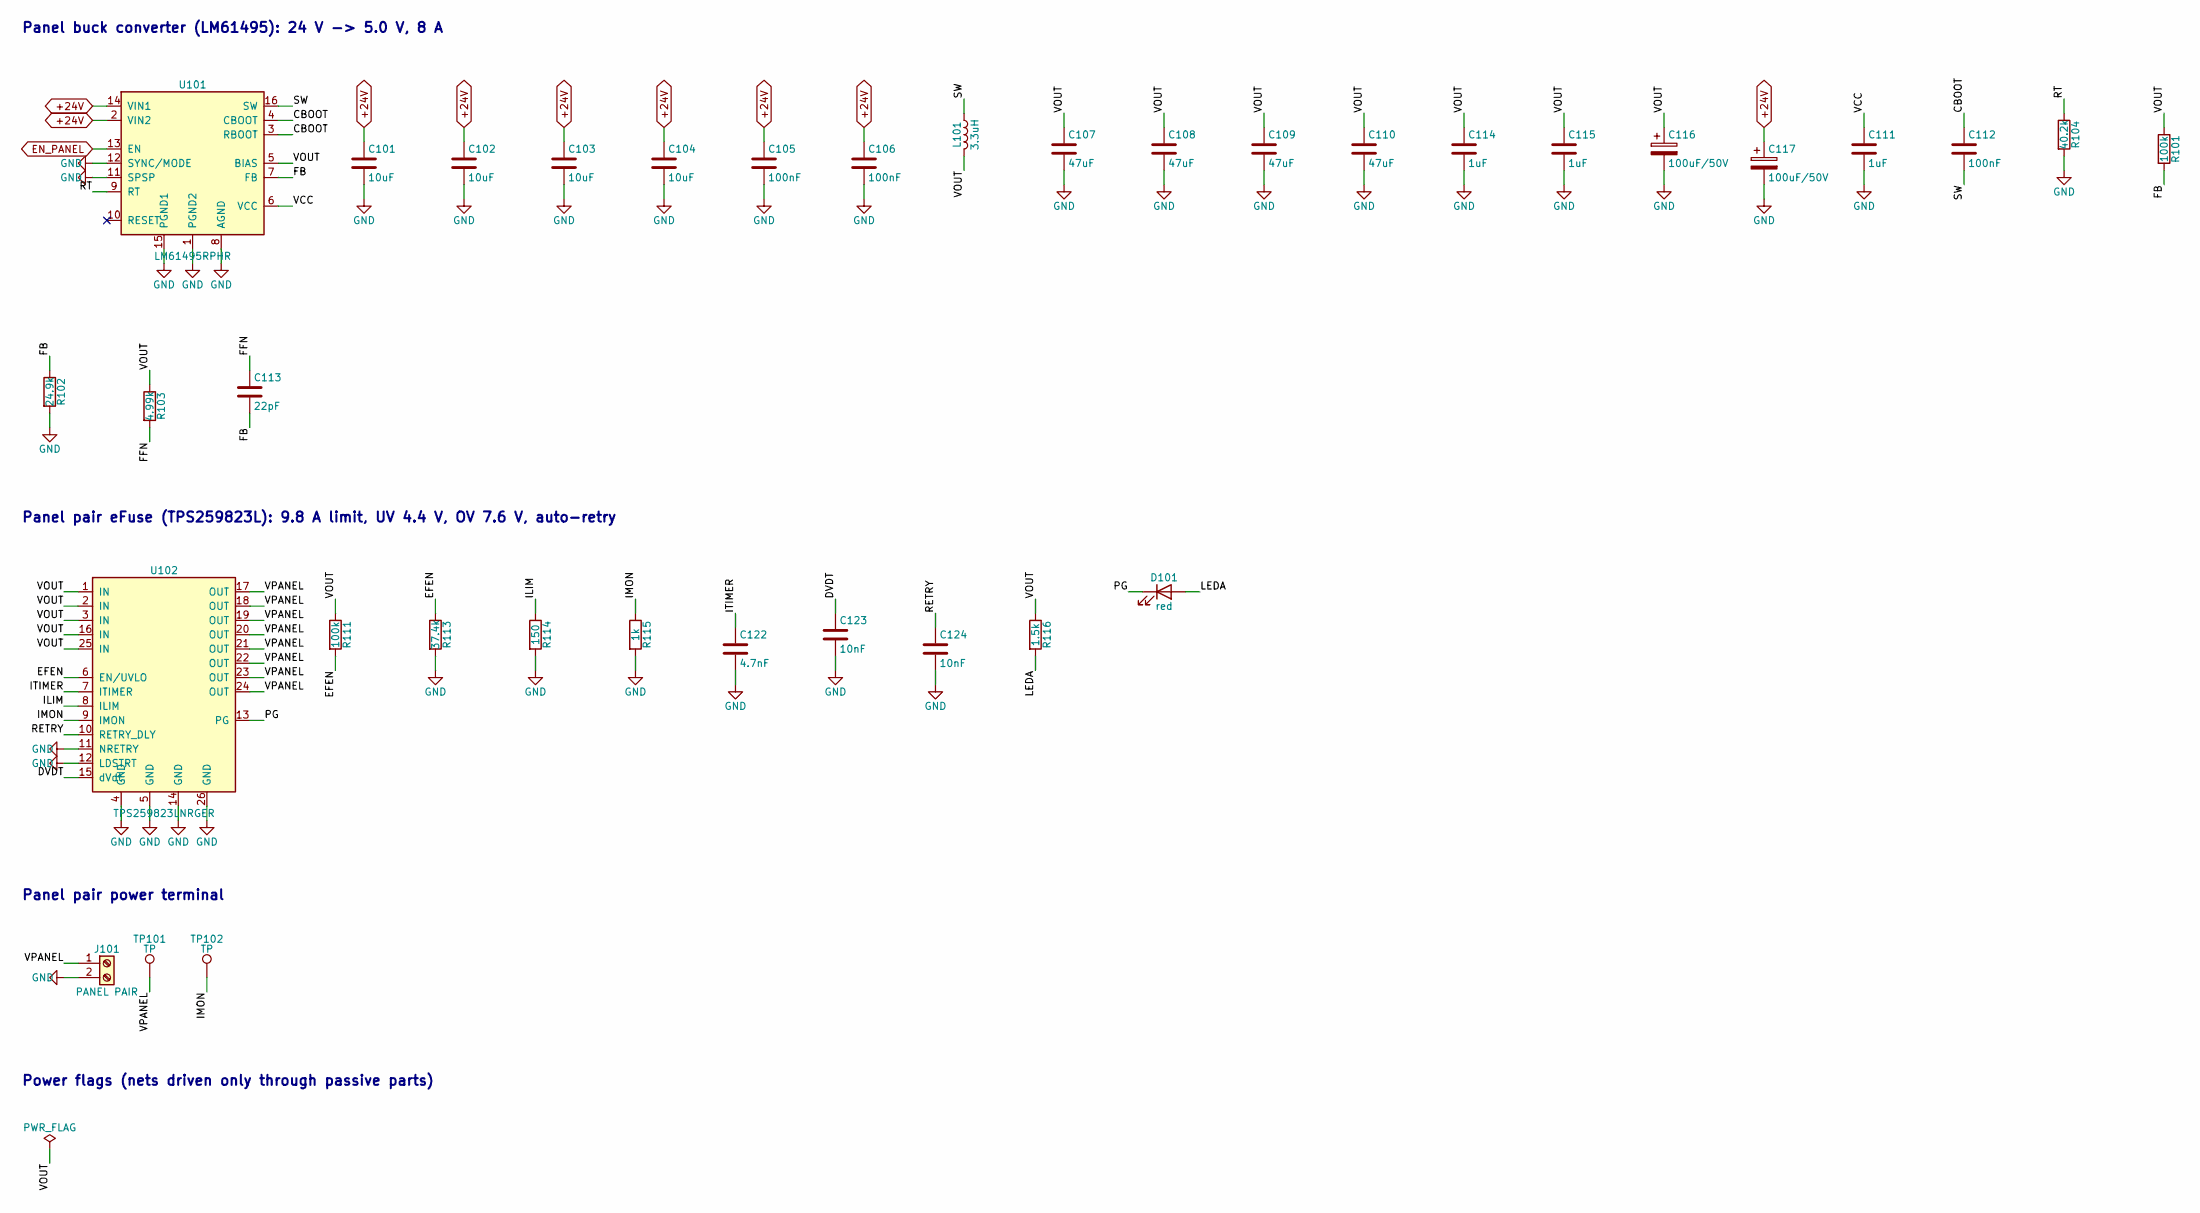
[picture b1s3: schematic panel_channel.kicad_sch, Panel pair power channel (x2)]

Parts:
C101, C102, C103, C104: 10uF; C_1210_3225Metric; Rating 50 V X7R; MPN GRM32ER71H106KA12L
C105, C106, C112: 100nF; C_0402_1005Metric; Rating 50 V X7R; MPN GRM155R71H104KE14D
C107, C108, C109, C110: 47uF; C_1210_3225Metric; Rating 10 V X7R; MPN GRM32ER71A476ME15L
C111, C114, C115: 1uF; C_0603_1608Metric; Rating 16 V X7R; MPN GRM188R71C105KA12D
C113: 22pF; C_0603_1608Metric; Rating 50 V C0G; MPN GRM1885C1H220JA01D
C116, C117: 100uF/50V; CP_Elec_8x10; Rating 50V; MPN EEE-FK1H101P
C122: 4.7nF; C_0603_1608Metric; Rating 50 V X7R; MPN GRM188R71H472KA01D
C123, C124: 10nF; C_0603_1608Metric; Rating 50 V X7R; MPN GRM188R71H103KA01D
D101: red; LED_0603_1608Metric; Rating 20 mA max, run at ~2 mA; MPN APT1608EC
J101: PANEL PAIR; TerminalBlock_Dinkle_DT-55-B01X-02_P10.00mm; Rating 10.00 mm pitch, M3.5, 24 A, 300 V; torq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; MPN DT-55-B01W-02
L101: 3.3uH; L_Bourns_SRP1050WA; Rating 3.3 uH +-20 %, Irms 18.7 A (40 K rise),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; MPN SRP1050WA-3R3M
R101, R111: 100k; R_0603_1608Metric; Tolerance 1%; Rating 0.1 W, 75 V; MPN RC0603FR-07100KL
R102: 24.9k; R_0603_1608Metric; Tolerance 1%; Rating 0.1 W, 75 V; MPN RC0603FR-0724K9L
R103: 4.99k; R_0603_1608Metric; Tolerance 1%; Rating 0.1 W, 75 V; MPN RC0603FR-074K99L
R104: 40.2k; R_0603_1608Metric; Tolerance 1%; Rating 0.1 W, 75 V; MPN RC0603FR-0740K2L
R113: 37.4k; R_0603_1608Metric; Tolerance 1%; Rating 0.1 W, 75 V; MPN RC0603FR-0737K4L
R114: 150; R_0603_1608Metric; Tolerance 1%; Rating 0.1 W, 75 V; MPN RC0603FR-07150RL
R115: 1k; R_0603_1608Metric; Tolerance 1%; Rating 0.1 W, 75 V; MPN RC0603FR-071KL
R116: 1.5k; R_0603_1608Metric; Tolerance 1%; Rating 0.1 W, 75 V; MPN RC0603FR-071K5L
TP101, TP102: TP; TestPoint_Pad_D1.5mm
U101: LM61495RPHR; TI_RPH0016B_VQFN-HR-16_3.5x4.5mm; Rating VIN 3-36 V (42 V transient), 10 A; used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; MPN LM61495RPHR
U102: TPS259823LNRGER; TI_RGE0024M_VQFN-24_4x4mm; Rating 2.7-24 V (30 V abs), RON 2.7/4.5 mOhm, 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; MPN TPS259823LNRGER

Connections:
+24V: C101.1, C102.1, C103.1, C104.1, C105.1, C106.1, C117.1, U101.2 (VIN2), U101.14 (VIN1); also elsewhere on the board
/Panel1/CBOOT: C112.1, U101.3 (RBOOT), U101.4 (CBOOT)
/Panel1/DVDT: C123.1, U102.15 (dVdt)
/Panel1/EFEN: R111.2, R113.1, U102.6 (EN/UVLO)
/Panel1/FB: C113.2, R101.2, R102.1, U101.7 (FB)
/Panel1/FFN: C113.1, R103.2
/Panel1/ILIM: R114.1, U102.8 (ILIM)
/Panel1/IMON: R115.1, TP102.1, U102.9 (IMON)
/Panel1/ITIMER: C122.1, U102.7 (ITIMER)
/Panel1/LEDA: D101.2 (A), R116.2
/Panel1/PG: D101.1 (K), U102.13 (PG)
/Panel1/RETRY: C124.1, U102.10 (RETRY_DLY)
/Panel1/RT: R104.1, U101.9 (RT)
/Panel1/SW: C112.2, L101.1, U101.16 (SW)
/Panel1/VCC: C111.1, U101.6 (VCC)
/Panel1/VOUT: C107.1, C108.1, C109.1, C110.1, C114.1, C115.1, C116.1, L101.2, R101.1, R103.1, R111.1, R116.1, U101.5 (BIAS), U102.1 (IN), U102.2 (IN), U102.3 (IN), U102.16 (IN), U102.25 (IN)
/Panel1/VPANEL: J101.1, TP101.1, U102.17 (OUT), U102.18 (OUT), U102.19 (OUT), U102.20 (OUT), U102.21 (OUT), U102.22 (OUT), U102.23 (OUT), U102.24 (OUT)
EN_PANEL: U101.13 (EN); also elsewhere on the board
GND: C101.2, C102.2, C103.2, C104.2, C105.2, C106.2, C107.2, C108.2, C109.2, C110.2, C111.2, C114.2, C115.2, C116.2, C117.2, C122.2, C123.2, C124.2, J101.2, R102.2, R104.2, R113.2, R114.2, R115.2, U101.1 (PGND2), U101.8 (AGND), U101.11 (SPSP), U101.12 (SYNC/MODE), U101.15 (PGND1), U102.4 (GND), U102.5 (GND), U102.11 (NRETRY), U102.12 (LDSTRT), U102.14 (GND), U102.26 (GND); also elsewhere on the board

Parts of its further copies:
C201, C202, C203, C204: 10uF; C_1210_3225Metric; Rating 50 V X7R; MPN GRM32ER71H106KA12L
C205, C206, C212: 100nF; C_0402_1005Metric; Rating 50 V X7R; MPN GRM155R71H104KE14D
C207, C208, C209, C210: 47uF; C_1210_3225Metric; Rating 10 V X7R; MPN GRM32ER71A476ME15L
C211, C214, C215: 1uF; C_0603_1608Metric; Rating 16 V X7R; MPN GRM188R71C105KA12D
C213: 22pF; C_0603_1608Metric; Rating 50 V C0G; MPN GRM1885C1H220JA01D
C216, C217: 100uF/50V; CP_Elec_8x10; Rating 50V; MPN EEE-FK1H101P
C222: 4.7nF; C_0603_1608Metric; Rating 50 V X7R; MPN GRM188R71H472KA01D
C223, C224: 10nF; C_0603_1608Metric; Rating 50 V X7R; MPN GRM188R71H103KA01D
D201: red; LED_0603_1608Metric; Rating 20 mA max, run at ~2 mA; MPN APT1608EC
J201: PANEL PAIR; TerminalBlock_Dinkle_DT-55-B01X-02_P10.00mm; Rating 10.00 mm pitch, M3.5, 24 A, 300 V; torq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; MPN DT-55-B01W-02
L201: 3.3uH; L_Bourns_SRP1050WA; Rating 3.3 uH +-20 %, Irms 18.7 A (40 K rise),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; MPN SRP1050WA-3R3M
R201, R211: 100k; R_0603_1608Metric; Tolerance 1%; Rating 0.1 W, 75 V; MPN RC0603FR-07100KL
R202: 24.9k; R_0603_1608Metric; Tolerance 1%; Rating 0.1 W, 75 V; MPN RC0603FR-0724K9L
R203: 4.99k; R_0603_1608Metric; Tolerance 1%; Rating 0.1 W, 75 V; MPN RC0603FR-074K99L
R204: 40.2k; R_0603_1608Metric; Tolerance 1%; Rating 0.1 W, 75 V; MPN RC0603FR-0740K2L
R213: 37.4k; R_0603_1608Metric; Tolerance 1%; Rating 0.1 W, 75 V; MPN RC0603FR-0737K4L
R214: 150; R_0603_1608Metric; Tolerance 1%; Rating 0.1 W, 75 V; MPN RC0603FR-07150RL
R215: 1k; R_0603_1608Metric; Tolerance 1%; Rating 0.1 W, 75 V; MPN RC0603FR-071KL
R216: 1.5k; R_0603_1608Metric; Tolerance 1%; Rating 0.1 W, 75 V; MPN RC0603FR-071K5L
TP201, TP202: TP; TestPoint_Pad_D1.5mm
U201: LM61495RPHR; TI_RPH0016B_VQFN-HR-16_3.5x4.5mm; Rating VIN 3-36 V (42 V transient), 10 A; used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; MPN LM61495RPHR
U202: TPS259823LNRGER; TI_RGE0024M_VQFN-24_4x4mm; Rating 2.7-24 V (30 V abs), RON 2.7/4.5 mOhm, 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; MPN TPS259823LNRGER

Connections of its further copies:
+24V: C201.1, C202.1, C203.1, C204.1, C205.1, C206.1, C217.1, U201.2 (VIN2), U201.14 (VIN1); also elsewhere on the board
/Panel2/CBOOT: C212.1, U201.3 (RBOOT), U201.4 (CBOOT)
/Panel2/DVDT: C223.1, U202.15 (dVdt)
/Panel2/EFEN: R211.2, R213.1, U202.6 (EN/UVLO)
/Panel2/FB: C213.2, R201.2, R202.1, U201.7 (FB)
/Panel2/FFN: C213.1, R203.2
/Panel2/ILIM: R214.1, U202.8 (ILIM)
/Panel2/IMON: R215.1, TP202.1, U202.9 (IMON)
/Panel2/ITIMER: C222.1, U202.7 (ITIMER)
/Panel2/LEDA: D201.2 (A), R216.2
/Panel2/PG: D201.1 (K), U202.13 (PG)
/Panel2/RETRY: C224.1, U202.10 (RETRY_DLY)
/Panel2/RT: R204.1, U201.9 (RT)
/Panel2/SW: C212.2, L201.1, U201.16 (SW)
/Panel2/VCC: C211.1, U201.6 (VCC)
/Panel2/VOUT: C207.1, C208.1, C209.1, C210.1, C214.1, C215.1, C216.1, L201.2, R201.1, R203.1, R211.1, R216.1, U201.5 (BIAS), U202.1 (IN), U202.2 (IN), U202.3 (IN), U202.16 (IN), U202.25 (IN)
/Panel2/VPANEL: J201.1, TP201.1, U202.17 (OUT), U202.18 (OUT), U202.19 (OUT), U202.20 (OUT), U202.21 (OUT), U202.22 (OUT), U202.23 (OUT), U202.24 (OUT)
EN_PANEL: U201.13 (EN); also elsewhere on the board
GND: C201.2, C202.2, C203.2, C204.2, C205.2, C206.2, C207.2, C208.2, C209.2, C210.2, C211.2, C214.2, C215.2, C216.2, C217.2, C222.2, C223.2, C224.2, J201.2, R202.2, R204.2, R213.2, R214.2, R215.2, U201.1 (PGND2), U201.8 (AGND), U201.11 (SPSP), U201.12 (SYNC/MODE), U201.15 (PGND1), U202.4 (GND), U202.5 (GND), U202.11 (NRETRY), U202.12 (LDSTRT), U202.14 (GND), U202.26 (GND); also elsewhere on the board

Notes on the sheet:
Panel buck converter (LM61495): 24 V -> 5.0 V, 8 A
Panel pair eFuse (TPS259823L): 9.8 A limit, UV 4.4 V, OV 7.6 V, auto-retry
Panel pair power terminal
Power flags (nets driven only through passive parts)

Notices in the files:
README.md:
License:
GPL-3.0. See [LICENSE](LICENSE).
License: GPL v3
